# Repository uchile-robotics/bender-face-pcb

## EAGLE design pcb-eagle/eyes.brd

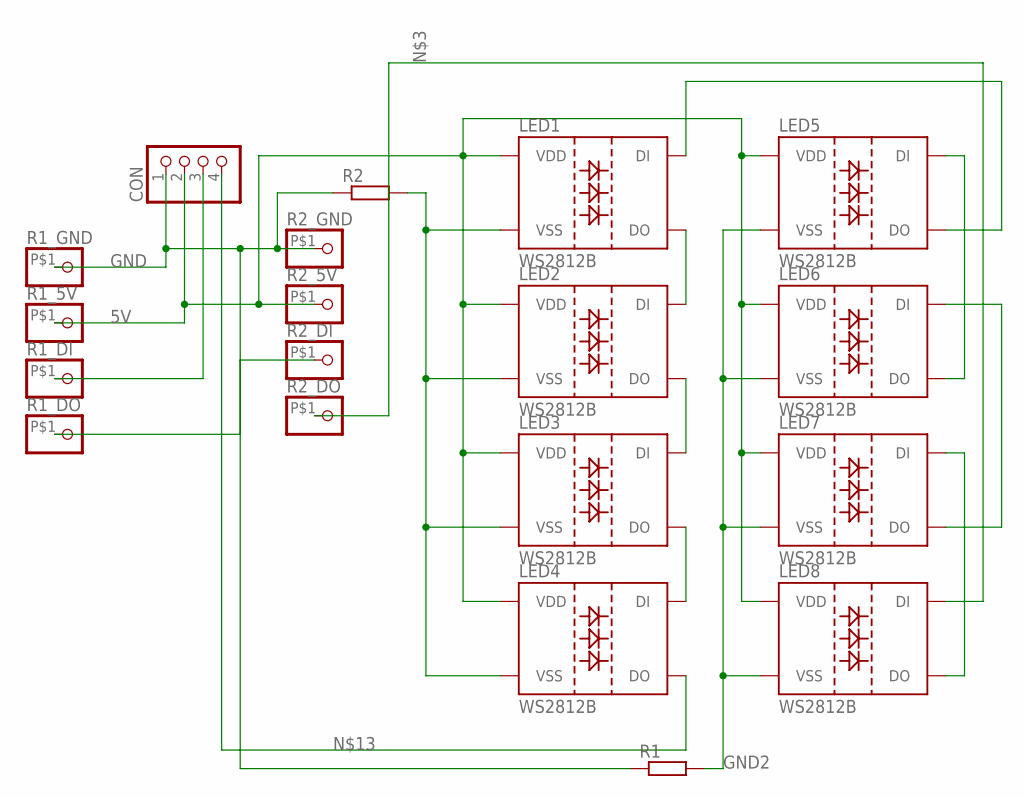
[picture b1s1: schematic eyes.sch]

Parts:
CON: PINHD-1X4; 1X04
LED1, LED2, LED3, LED4, LED5, LED6, LED7, LED8: WS2812B
R1, R2: R-EU_0207/7; 0207/7
R1_5V, R1_DI, R1_DO, R1_GND, R2_5V, R2_DI, R2_DO, R2_GND: PINHD-1X1-BIGPOGO; 1X1-BIGPOGO

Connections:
5V: CON.2, LED1.1 (VDD), LED2.1 (VDD), LED3.1 (VDD), LED4.1 (VDD), LED5.1 (VDD), LED6.1 (VDD), LED7.1 (VDD), LED8.1 (VDD), R1_5V.P$1, R2_5V.P$1
GND: CON.1, R1.1, R1_GND.P$1, R2.1, R2_GND.P$1
GND2: LED5.3 (VSS), LED6.3 (VSS), LED7.3 (VSS), LED8.3 (VSS), R1.2
GND3: LED1.3 (VSS), LED2.3 (VSS), LED3.3 (VSS), LED4.3 (VSS), R2.2
unnamed: CON.3, R1_DI.P$1
unnamed: LED8.4 (DI), R2_DO.P$1
unnamed: R1_DO.P$1, R2_DI.P$1
unnamed: LED7.4 (DI), LED8.2 (DO)
unnamed: LED6.4 (DI), LED7.2 (DO)
unnamed: LED5.4 (DI), LED6.2 (DO)
unnamed: LED1.2 (DO), LED2.4 (DI)
unnamed: LED2.2 (DO), LED3.4 (DI)
unnamed: LED3.2 (DO), LED4.4 (DI)
unnamed: CON.4, LED4.2 (DO)
unnamed: LED1.4 (DI), LED5.2 (DO)

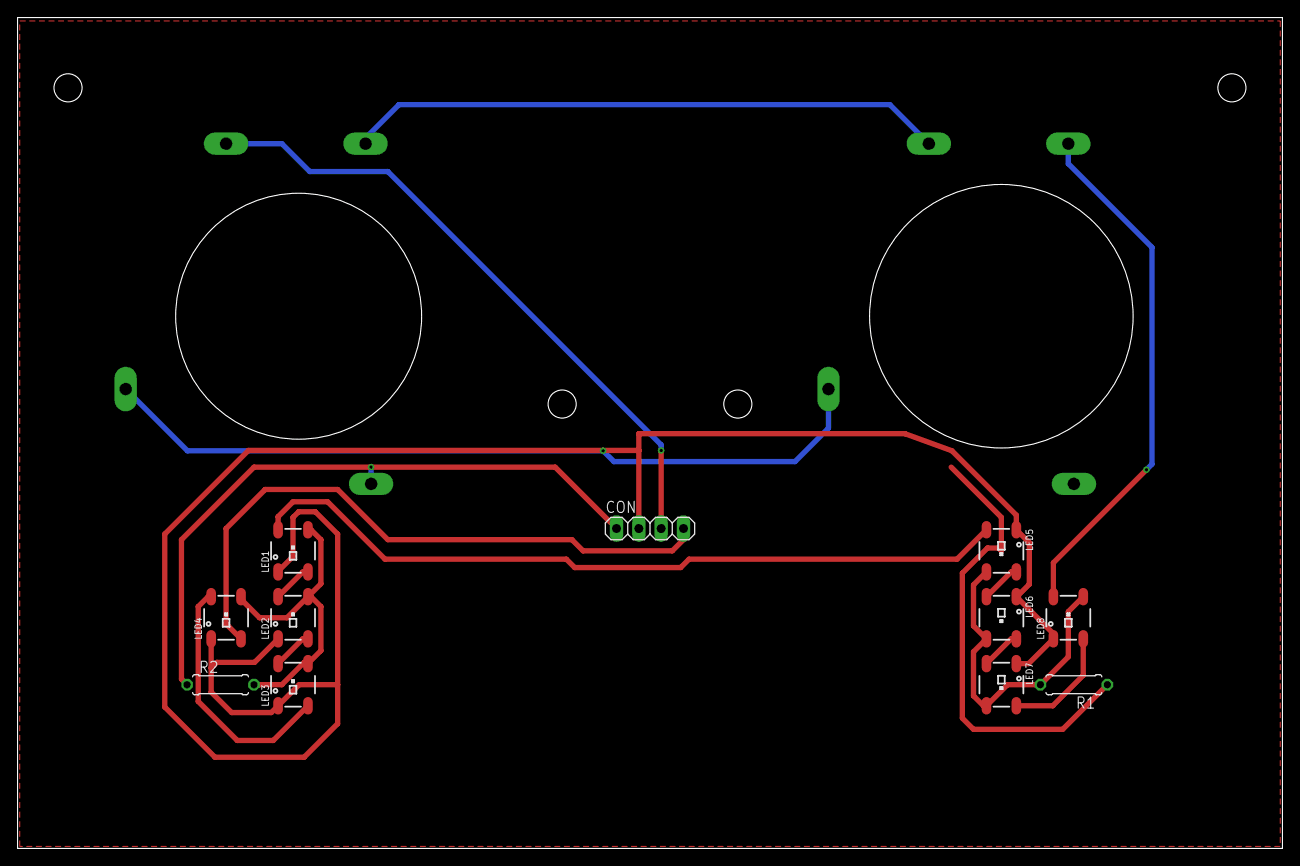
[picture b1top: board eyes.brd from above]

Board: 2 copper layers, 144.0 x 94.6 mm, 19 parts (0 on the bottom side), 15 nets.

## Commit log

2022-04-22 Initialize project
2022-04-22 Testing metrics for the PCB on the Board File
2022-09-20 added completed eagle version
